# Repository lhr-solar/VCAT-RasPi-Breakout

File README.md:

# Controls-RasPi-Breakout

This is the PCB that will interface with the Raspberry Pi Compute Module 4.

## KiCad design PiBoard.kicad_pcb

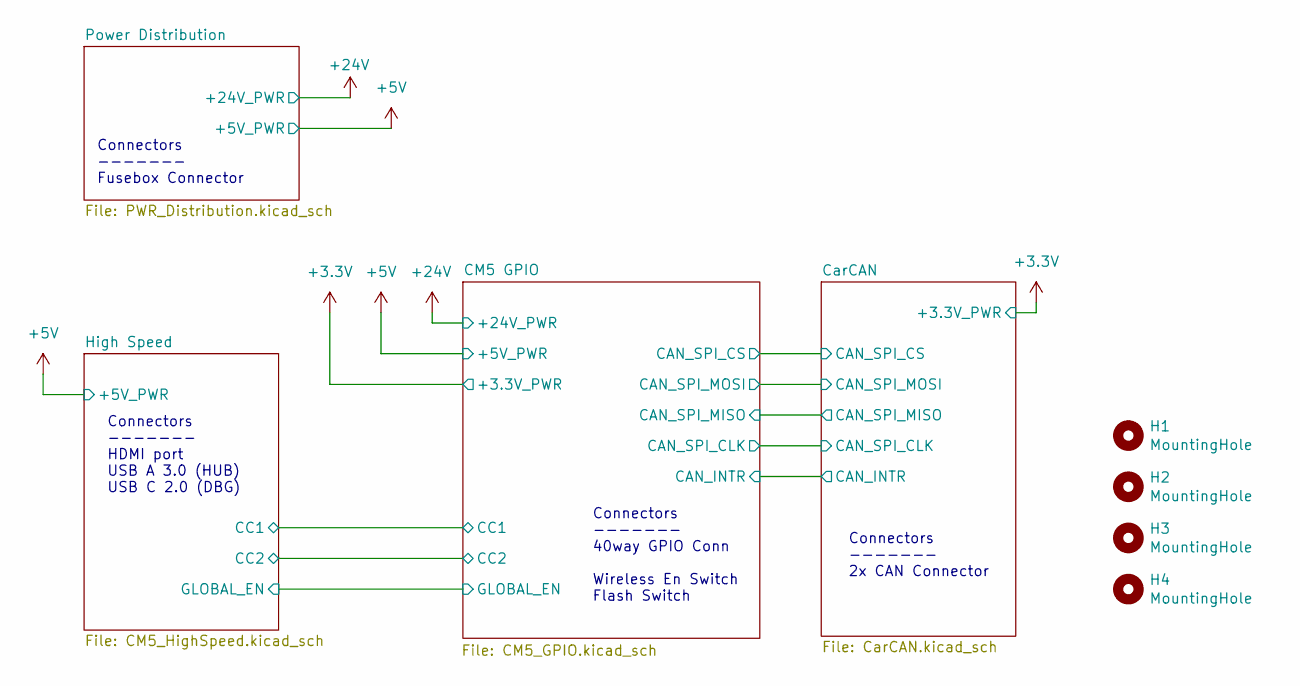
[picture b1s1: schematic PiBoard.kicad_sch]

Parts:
H1, H2, H3, H4: MountingHole; MountingHole_3.2mm_M3; JLC N/A

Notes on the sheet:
Connectors ------- HDMI port USB A 3.0 (HUB) USB C 2.0 (DBG)
Connectors ------- Fusebox Connector
Connectors ------- 2x CAN Connector
Connectors ------- 40way GPIO Conn Wireless En Switch Flash Switch

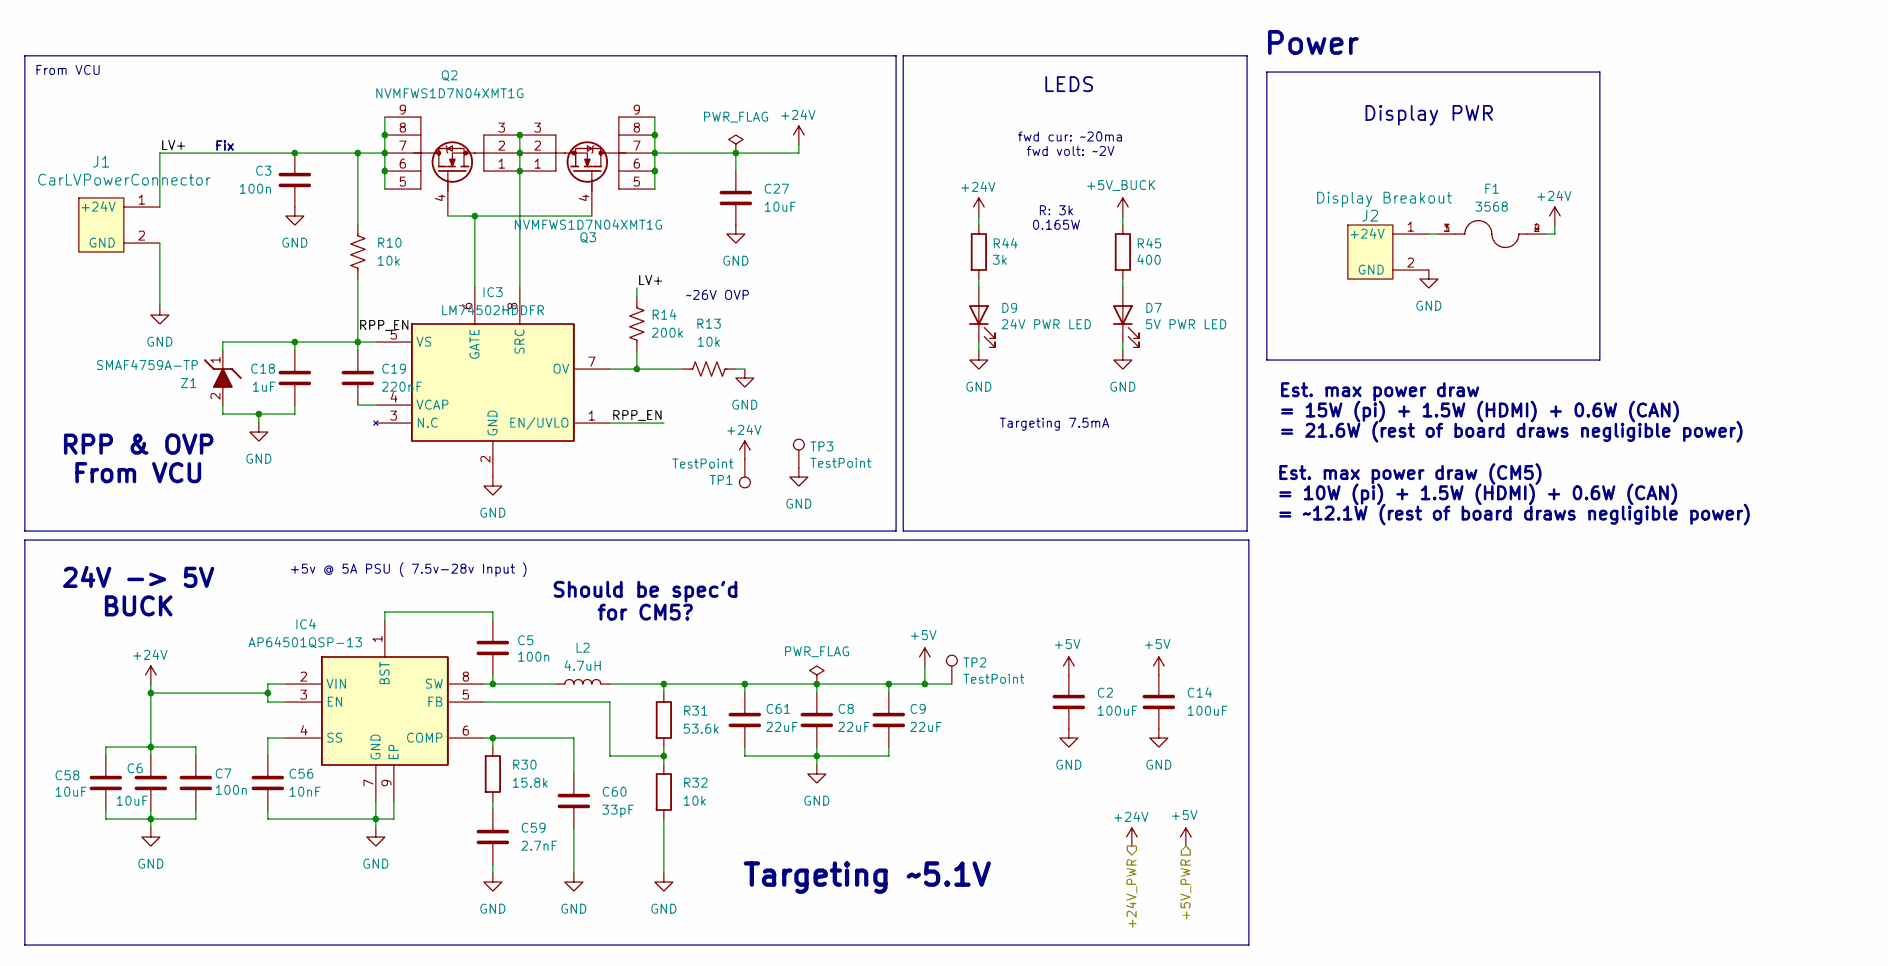
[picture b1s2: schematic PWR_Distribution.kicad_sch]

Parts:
C2, C14: 100uF; C_1206_3216Metric_Pad1.33x1.80mm_HandSolder; JLC C7432784
C3, C5, C7: 100n; C_0603_1608Metric_Pad1.08x0.95mm_HandSolder; JLC C14663
C6, C27, C58: 10uF; C_0805_2012Metric_Pad1.18x1.45mm_HandSolder; JLC C440198
C8, C9, C61: 22uF; C_0805_2012Metric_Pad1.18x1.45mm_HandSolder; JLC C338078
C18: 1uF; C_0805_2012Metric_Pad1.18x1.45mm_HandSolder; JLC C28323
C19: 220nF; C_0805_2012Metric_Pad1.18x1.45mm_HandSolder; JLC C21120
C56: 10nF; C_0603_1608Metric_Pad1.08x0.95mm_HandSolder; JLC C1589
C59: 2.7nF; C_0603_1608Metric_Pad1.08x0.95mm_HandSolder; JLC C107085
C60: 33pF; C_0603_1608Metric_Pad1.08x0.95mm_HandSolder; JLC C1663
D7: 5V PWR LED; LED_0603_1608Metric_Pad1.05x0.95mm_HandSolder; JLC C2289
D9: 24V PWR LED; LED_0603_1608Metric_Pad1.05x0.95mm_HandSolder; JLC C2289
F1: 3568; FUSE_3568; PARTREV C
IC3: LM74502HDDFR; SOT65P280X110-8N; Mouser Part Number 595-LM74502HDDFR
IC4: AP64501QSP-13; SOIC127P600X163-9N; JLC C2071517
J1: CarLVPowerConnector; Molex_Nano-Fit_105309-xx02_1x02_P2.50mm_Vertical; JLC N/A
J2: Display Breakout; Molex_Nano-Fit_105309-xx02_1x02_P2.50mm_Vertical; JLC N/A
L2: 4.7uH; INDPM110100X540N; JLC C5189748
Q2, Q3: NVMFWS1D7N04XMT1G; NVMFWS3D0P04M8LT1G; Manufacturer_Part_Number NVMFWS1D7N04XMT1G; JLC C52190853
R10, R13: 10k; R_0603_1608Metric_Pad0.98x0.95mm_HandSolder; JLC C25804
R14: 200k; R_0603_1608Metric_Pad0.98x0.95mm_HandSolder; JLC C25811
R30: 15.8k; R_0805_2012Metric_Pad1.20x1.40mm_HandSolder; JLC C17468
R31: 53.6k; R_0805_2012Metric_Pad1.20x1.40mm_HandSolder; JLC C2930115
R32: 10k; R_0805_2012Metric; JLC C17414
R44: 3k; R_0603_1608Metric_Pad0.98x0.95mm_HandSolder; JLC C445829
R45: 400; R_0603_1608Metric_Pad0.98x0.95mm_HandSolder; JLC C5841024
TP1, TP2, TP3: TestPoint; TestPoint_Pad_2.0x2.0mm; JLC N/A
Z1: SMAF4759A-TP; D_SMA; Mouser Part Number 833-SMAF4749A-TP

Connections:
+5V: C2.1, C8.1, C9.1, C14.1, C61.1, L2.2, R31.1, TP2.1; also elsewhere on the board
+5V_BUCK: R45.1
+24V: C6.1, C7.1, C27.1, C58.1, F1.2, F1.4, IC4.2 (VIN), IC4.3 (EN), Q3.5, Q3.6, Q3.7, Q3.8, Q3.9, R44.1, TP1.1
/Power Distribution/LV+: C3.2, J1.1 (+24V), Q2.5, Q2.6, Q2.7, Q2.8, Q2.9, R10.1, R14.1
/Power Distribution/RPP_EN: C18.2, C19.1, IC3.1 (EN/UVLO), IC3.5 (VS), R10.2, Z1.1 (K)
GND: C2.2, C3.1, C6.2, C7.2, C8.2, C9.2, C14.2, C18.1, C27.2, C56.2, C58.2, C59.2, C60.2, C61.2, D7.1 (K), D9.1 (K), IC3.2 (GND), IC4.7 (GND), IC4.9 (EP), J1.2 (GND), J2.2 (GND), R13.2, R32.2, TP3.1, Z1.2 (A); also elsewhere on the board
unnamed: C59.1, R30.2
unnamed: D7.2 (A), R45.2
unnamed: D9.2 (A), R44.2
unnamed: IC3.6 (GATE), Q2.4, Q3.4
unnamed: IC3.7 (OV), R13.1, R14.2
unnamed: IC3.8 (SRC), Q2.1, Q2.2, Q2.3, Q3.1, Q3.2, Q3.3
unnamed: C19.2, IC3.4 (VCAP)
unnamed: C5.1, IC4.1 (BST)
unnamed: C60.1, IC4.6 (COMP), R30.1
unnamed: IC4.5 (FB), R31.2, R32.1
unnamed: C56.1, IC4.4 (SS)
unnamed: C5.2, IC4.8 (SW), L2.1
unnamed: F1.1, F1.3, J2.1 (+24V)

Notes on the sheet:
Est. max power draw (CM5) = 10W (pi) + 1.5W (HDMI) + 0.6W (CAN) = ~12.1W (rest of board draws negligible power)
RPP & OVP From VCU
Fix
From VCU
Display PWR
Est. max power draw = 15W (pi) + 1.5W (HDMI) + 0.6W (CAN) = 21.6W (rest of board draws negligible power)
Targeting ~5.1V
Should be spec'd for CM5?
+5v @ 5A PSU ( 7.5v-28v Input )
~26V OVP
R: 3k 0.165W
LEDS
fwd cur: ~20ma fwd volt: ~2V
Targeting 7.5mA
Power
24V -> 5V BUCK

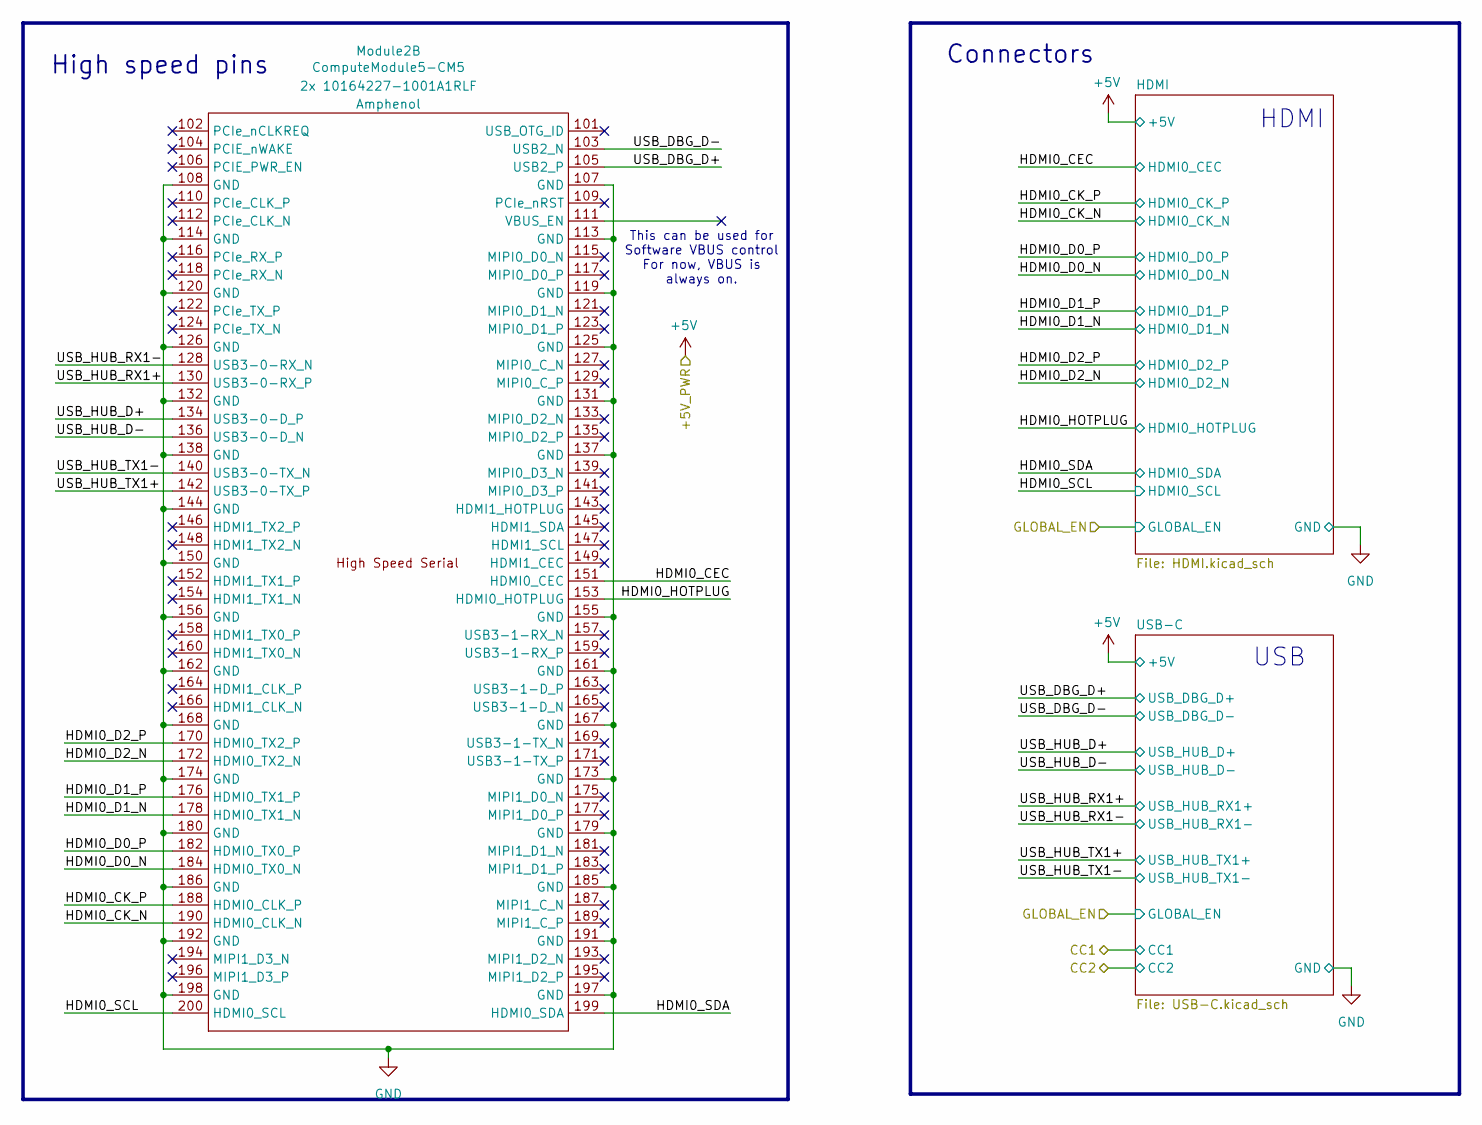
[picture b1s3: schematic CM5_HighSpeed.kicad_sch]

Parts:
Module2: ComputeModule5-CM5; Raspberry-Pi-5-Compute-Module; Part Description 100 Position Connector Receptacle, Cent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; JLC C6782225

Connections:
/High Speed/HDMI0_CEC: Module2.151 (HDMI0_CEC); also elsewhere on the board
/High Speed/HDMI0_CK_N: Module2.190 (HDMI0_CLK_N); also elsewhere on the board
/High Speed/HDMI0_CK_P: Module2.188 (HDMI0_CLK_P); also elsewhere on the board
/High Speed/HDMI0_D0_N: Module2.184 (HDMI0_TX0_N); also elsewhere on the board
/High Speed/HDMI0_D0_P: Module2.182 (HDMI0_TX0_P); also elsewhere on the board
/High Speed/HDMI0_D1_N: Module2.178 (HDMI0_TX1_N); also elsewhere on the board
/High Speed/HDMI0_D1_P: Module2.176 (HDMI0_TX1_P); also elsewhere on the board
/High Speed/HDMI0_D2_N: Module2.172 (HDMI0_TX2_N); also elsewhere on the board
/High Speed/HDMI0_D2_P: Module2.170 (HDMI0_TX2_P); also elsewhere on the board
/High Speed/HDMI0_HOTPLUG: Module2.153 (HDMI0_HOTPLUG); also elsewhere on the board
/High Speed/HDMI0_SCL: Module2.200 (HDMI0_SCL); also elsewhere on the board
/High Speed/HDMI0_SDA: Module2.199 (HDMI0_SDA); also elsewhere on the board
/High Speed/USB_DBG_D+: Module2.105 (USB2_P); also elsewhere on the board
/High Speed/USB_DBG_D-: Module2.103 (USB2_N); also elsewhere on the board
/High Speed/USB_HUB_D+: Module2.134 (USB3-0-D_P); also elsewhere on the board
/High Speed/USB_HUB_D-: Module2.136 (USB3-0-D_N); also elsewhere on the board
/High Speed/USB_HUB_RX1+: Module2.130 (USB3-0-RX_P); also elsewhere on the board
/High Speed/USB_HUB_RX1-: Module2.128 (USB3-0-RX_N); also elsewhere on the board
/High Speed/USB_HUB_TX1+: Module2.142 (USB3-0-TX_P); also elsewhere on the board
/High Speed/USB_HUB_TX1-: Module2.140 (USB3-0-TX_N); also elsewhere on the board
GND: Module2.107 (GND), Module2.108 (GND), Module2.113 (GND), Module2.114 (GND), Module2.119 (GND), Module2.120 (GND), Module2.125 (GND), Module2.126 (GND), Module2.131 (GND), Module2.132 (GND), Module2.137 (GND), Module2.138 (GND), Module2.144 (GND), Module2.150 (GND), Module2.155 (GND), Module2.156 (GND), Module2.161 (GND), Module2.162 (GND), Module2.167 (GND), Module2.168 (GND), Module2.173 (GND), Module2.174 (GND), Module2.179 (GND), Module2.180 (GND), Module2.185 (GND), Module2.186 (GND), Module2.191 (GND), Module2.192 (GND), Module2.197 (GND), Module2.198 (GND); also elsewhere on the board

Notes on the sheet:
This can be used for Software VBUS control For now, VBUS is always on.
USB
Connectors
High speed pins
HDMI

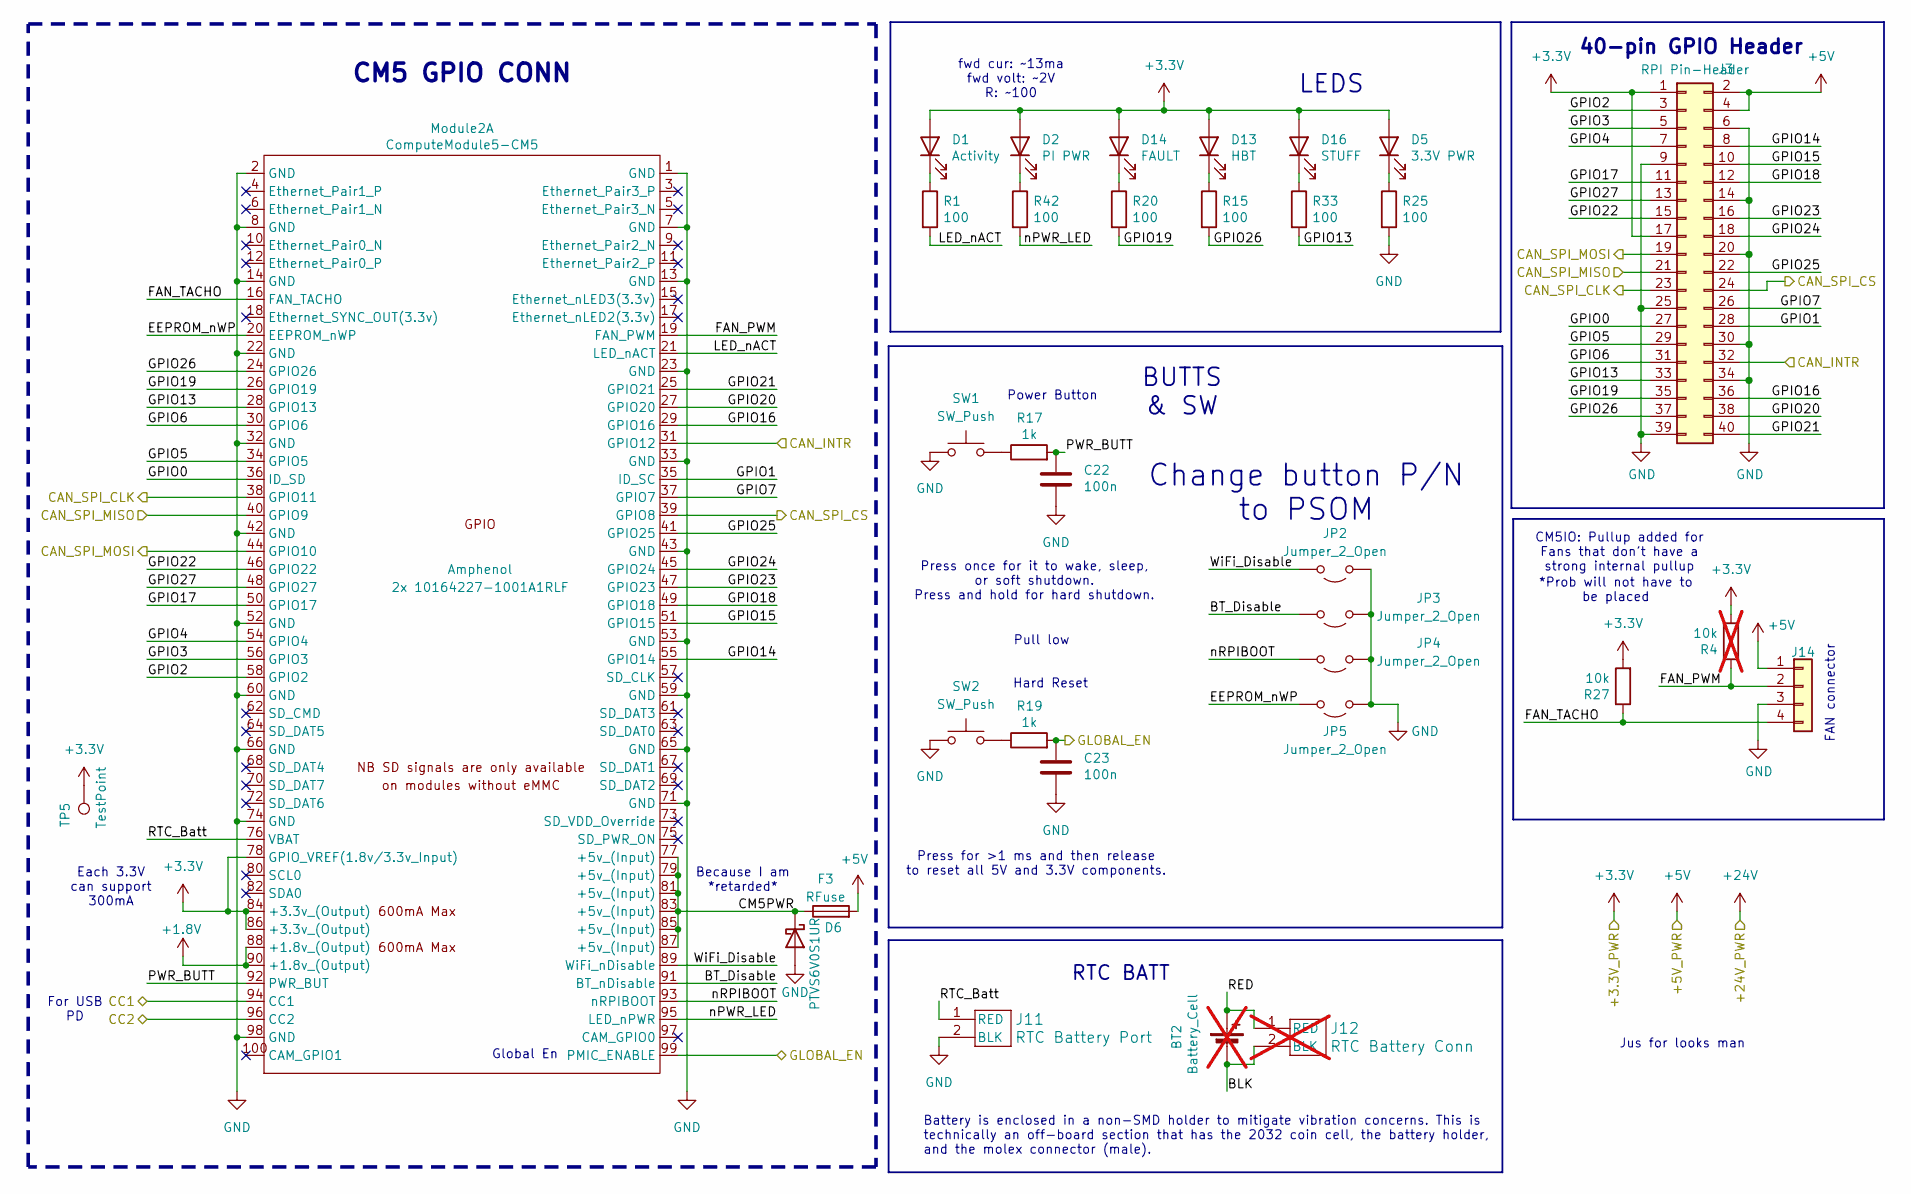
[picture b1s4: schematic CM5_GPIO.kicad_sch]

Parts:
BT2: Battery_Cell; JLC N/A; not fitted
C22, C23: 100n; C_0603_1608Metric_Pad1.08x0.95mm_HandSolder; JLC C14663
D1: Activity; LED_0603_1608Metric_Pad1.05x0.95mm_HandSolder; JLC C2289
D2: PI PWR; LED_0603_1608Metric_Pad1.05x0.95mm_HandSolder; JLC C2289
D5: 3.3V PWR; LED_0603_1608Metric_Pad1.05x0.95mm_HandSolder; JLC C2289
D6: PTVS6V0S1UR; D_SOD-123; JLC C18723426
D13: HBT; LED_0603_1608Metric_Pad1.05x0.95mm_HandSolder; JLC C2289
D14: FAULT; LED_0603_1608Metric_Pad1.05x0.95mm_HandSolder; JLC C2286
D16: STUFF; LED_0603_1608Metric_Pad1.05x0.95mm_HandSolder; JLC C2289
F3: RFuse; Fuse_1206_3216Metric_Pad1.42x1.75mm_HandSolder; JLC C42449089
J3: RPI Pin-Header; PinSocket_2x20_P2.54mm_Vertical; JLC N/A
J11: RTC Battery Port; CONN02_530470210_MOL; JLC N/A
J12: RTC Battery Conn; CONN02_530470210_MOL; JLC N/A; not fitted
J14: Fan Header; JST_SH_BM04B-SRSS-TB_1x04-1MP_P1.00mm_Vertical; Part Description 4 pin vertical 1mm pitch connector; JLC N/A
JP2, JP3, JP4, JP5: Jumper_2_Open; PinHeader_1x02_P2.54mm_Vertical; JLC N/A
Module2: ComputeModule5-CM5; Raspberry-Pi-5-Compute-Module; Part Description 100 Position Connector Receptacle, Cent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; JLC C6782225
R1, R15, R20, R25, R33, R42: 100; R_0603_1608Metric_Pad0.98x0.95mm_HandSolder; JLC C22775
R4: 10k; R_0603_1608Metric_Pad0.98x0.95mm_HandSolder; Part Description Resistor 10K M1005 1% 63mW; JLC C25804; not fitted
R17, R19: 1k; R_0603_1608Metric_Pad0.98x0.95mm_HandSolder; JLC C21190
R27: 10k; R_0603_1608Metric_Pad0.98x0.95mm_HandSolder; Part Description Resistor 10K M1005 1% 63mW; JLC C25804
SW1, SW2: SW_Push; TL3365AF180QG; JLC C2886926
TP5: TestPoint; TestPoint_Pad_2.0x2.0mm; JLC N/A

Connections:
+1.8V: Module2.88 (+1.8v_(Output)), Module2.90 (+1.8v_(Output))
+3.3V: D1.2 (A), D2.2 (A), D5.2 (A), D13.2 (A), D14.2 (A), D16.2 (A), J3.1, J3.17, Module2.78 (GPIO_VREF(1.8v/3.3v_Input)), Module2.84 (+3.3v_(Output)), Module2.86 (+3.3v_(Output)), R4.2, R27.2, TP5.1; also elsewhere on the board
+5V: F3.2, J3.2, J3.4, J14.1; also elsewhere on the board
/CM5 GPIO/BT_Disable: JP3.2 (B), Module2.91 (BT_nDisable)
/CM5 GPIO/CAN_INTR: J3.32, Module2.31 (GPIO12); also elsewhere on the board
/CM5 GPIO/CAN_SPI_CLK: J3.23, Module2.38 (GPIO11); also elsewhere on the board
/CM5 GPIO/CAN_SPI_CS: J3.24, Module2.39 (GPIO8); also elsewhere on the board
/CM5 GPIO/CAN_SPI_MISO: J3.21, Module2.40 (GPIO9); also elsewhere on the board
/CM5 GPIO/CAN_SPI_MOSI: J3.19, Module2.44 (GPIO10); also elsewhere on the board
/CM5 GPIO/CC1: Module2.94 (CC1); also elsewhere on the board
/CM5 GPIO/CC2: Module2.96 (CC2); also elsewhere on the board
/CM5 GPIO/CM5PWR: D6.1 (K), F3.1, Module2.77 (+5v_(Input)), Module2.79 (+5v_(Input)), Module2.81 (+5v_(Input)), Module2.83 (+5v_(Input)), Module2.85 (+5v_(Input)), Module2.87 (+5v_(Input))
/CM5 GPIO/EEPROM_nWP: JP5.2 (B), Module2.20 (EEPROM_nWP)
/CM5 GPIO/FAN_PWM: J14.2, Module2.19 (FAN_PWM), R4.1
/CM5 GPIO/FAN_TACHO: J14.4, Module2.16 (FAN_TACHO), R27.1
/CM5 GPIO/GLOBAL_EN: C23.1, Module2.99 (PMIC_ENABLE), R19.2; also elsewhere on the board
/CM5 GPIO/GPIO0: J3.27, Module2.36 (ID_SD)
/CM5 GPIO/GPIO1: J3.28, Module2.35 (ID_SC)
/CM5 GPIO/GPIO2: J3.3, Module2.58 (GPIO2)
/CM5 GPIO/GPIO3: J3.5, Module2.56 (GPIO3)
/CM5 GPIO/GPIO4: J3.7, Module2.54 (GPIO4)
/CM5 GPIO/GPIO5: J3.29, Module2.34 (GPIO5)
/CM5 GPIO/GPIO6: J3.31, Module2.30 (GPIO6)
/CM5 GPIO/GPIO7: J3.26, Module2.37 (GPIO7)
/CM5 GPIO/GPIO13: J3.33, Module2.28 (GPIO13), R33.2
/CM5 GPIO/GPIO14: J3.8, Module2.55 (GPIO14)
/CM5 GPIO/GPIO15: J3.10, Module2.51 (GPIO15)
/CM5 GPIO/GPIO16: J3.36, Module2.29 (GPIO16)
/CM5 GPIO/GPIO17: J3.11, Module2.50 (GPIO17)
/CM5 GPIO/GPIO18: J3.12, Module2.49 (GPIO18)
/CM5 GPIO/GPIO19: J3.35, Module2.26 (GPIO19), R20.2
/CM5 GPIO/GPIO20: J3.38, Module2.27 (GPIO20)
/CM5 GPIO/GPIO21: J3.40, Module2.25 (GPIO21)
/CM5 GPIO/GPIO22: J3.15, Module2.46 (GPIO22)
/CM5 GPIO/GPIO23: J3.16, Module2.47 (GPIO23)
/CM5 GPIO/GPIO24: J3.18, Module2.45 (GPIO24)
/CM5 GPIO/GPIO25: J3.22, Module2.41 (GPIO25)
/CM5 GPIO/GPIO26: J3.37, Module2.24 (GPIO26), R15.2
/CM5 GPIO/GPIO27: J3.13, Module2.48 (GPIO27)
/CM5 GPIO/LED_nACT: Module2.21 (LED_nACT), R1.2
/CM5 GPIO/PWR_BUTT: C22.1, Module2.92 (PWR_BUT), R17.2
/CM5 GPIO/RTC_Batt: J11.1 (RED), Module2.76 (VBAT)
/CM5 GPIO/WiFi_Disable: JP2.2 (B), Module2.89 (WiFi_nDisable)
/CM5 GPIO/nPWR_LED: Module2.95 (LED_nPWR), R42.2
/CM5 GPIO/nRPIBOOT: JP4.2 (B), Module2.93 (nRPIBOOT)
GND: C22.2, C23.2, D6.2 (A), J3.6, J3.9, J3.14, J3.20, J3.25, J3.30, J3.34, J3.39, J11.2 (BLK), J14.3, JP2.1 (A), JP3.1 (A), JP4.1 (A), JP5.1 (A), Module2.1 (GND), Module2.2 (GND), Module2.7 (GND), Module2.8 (GND), Module2.13 (GND), Module2.14 (GND), Module2.22 (GND), Module2.23 (GND), Module2.32 (GND), Module2.33 (GND), Module2.42 (GND), Module2.43 (GND), Module2.52 (GND), Module2.53 (GND), Module2.59 (GND), Module2.60 (GND), Module2.65 (GND), Module2.66 (GND), Module2.71 (GND), Module2.74 (GND), Module2.98 (GND), R25.2, SW1.1, SW2.1; also elsewhere on the board
unnamed: BT2.1 (+), J12.1 (RED)
unnamed: BT2.2 (-), J12.2 (BLK)
unnamed: D1.1 (K), R1.1
unnamed: D2.1 (K), R42.1
unnamed: D5.1 (K), R25.1
unnamed: D13.1 (K), R15.1
unnamed: D14.1 (K), R20.1
unnamed: D16.1 (K), R33.1
unnamed: R17.1, SW1.2
unnamed: R19.1, SW2.2

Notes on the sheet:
Press once for it to wake, sleep, or soft shutdown. Press and hold for hard shutdown.
Power Button
FAN connector
fwd cur: ~13ma fwd volt: ~2V R: ~100
*Prob will not have to be placed
LEDS
Battery is enclosed in a non-SMD holder to mitigate vibration concerns. This is technically an off-board section that has the 2032 coin cell, the battery holder, and the molex connector (male).
Change button P/N to PSOM
Global En
For USB PD
40-pin GPIO Header
Each 3.3V can support 300mA
Because I am *retarded*
Jus for looks man
CM5 GPIO CONN
Hard Reset
BUTTS & SW
Press for >1 ms and then release to reset all 5V and 3.3V components.
CM5IO: Pullup added for Fans that don't have a strong internal pullup
Pull low
RTC BATT

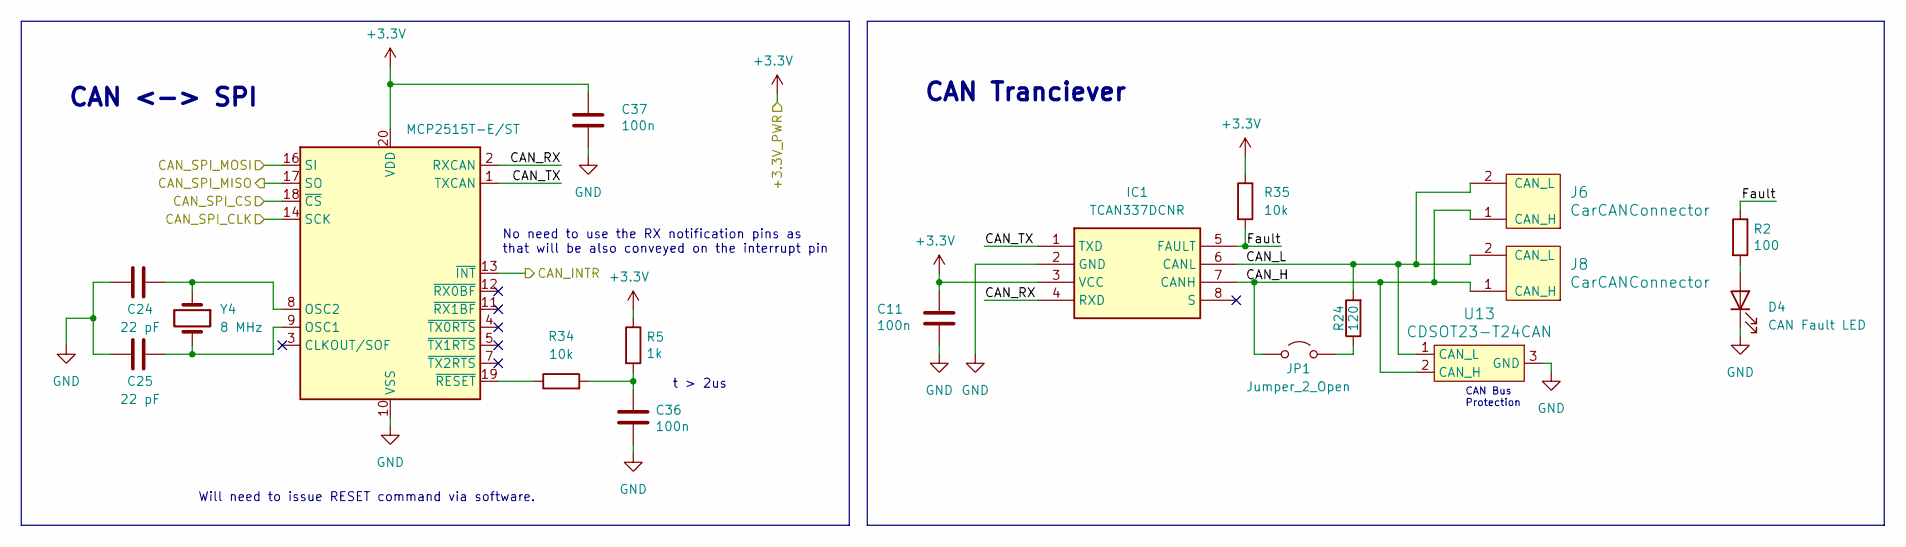
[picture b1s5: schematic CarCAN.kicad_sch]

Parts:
C11, C36, C37: 100n; C_0603_1608Metric_Pad1.08x0.95mm_HandSolder; JLC C14663
C24, C25: 22 pF; C_0603_1608Metric_Pad1.08x0.95mm_HandSolder; JLC C1653
D4: CAN Fault LED; LED_0603_1608Metric_Pad1.05x0.95mm_HandSolder; JLC C2286
IC1: TCAN337DCNR; SOT65P280X145-8N; JLC C130129
J6, J8: CarCANConnector; Molex_Nano-Fit_105309-xx02_1x02_P2.50mm_Vertical; JLC N/A
JP1: Jumper_2_Open; PinHeader_1x02_P2.54mm_Vertical; JLC N/A
R2: 100; R_0603_1608Metric_Pad0.98x0.95mm_HandSolder; JLC C22775
R5: 1k; R_0603_1608Metric_Pad0.98x0.95mm_HandSolder; JLC C21190
R24: 120; R_0603_1608Metric_Pad0.98x0.95mm_HandSolder; JLC C22787
R34, R35: 10k; R_0603_1608Metric_Pad0.98x0.95mm_HandSolder; JLC C25804
U13: CDSOT23-T24CAN; SOT-23W; JLC C2959841
U14: MCP2515T-E/ST; TSSOP-20_4.4x6.5mm_P0.65mm; JLC C627064
Y4: 8 MHz; ABM3; JLC C144380

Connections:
+3.3V: C11.1, C37.1, IC1.3 (VCC), R5.1, R35.1, U14.20 (VDD); also elsewhere on the board
/CM5 GPIO/CAN_INTR: U14.13 (~INT); also elsewhere on the board
/CM5 GPIO/CAN_SPI_CLK: U14.14 (SCK); also elsewhere on the board
/CM5 GPIO/CAN_SPI_CS: U14.18 (~CS); also elsewhere on the board
/CM5 GPIO/CAN_SPI_MISO: U14.17 (SO); also elsewhere on the board
/CM5 GPIO/CAN_SPI_MOSI: U14.16 (SI); also elsewhere on the board
/CarCAN/CAN_H: IC1.7 (CANH), J6.1 (CAN_H), J8.1 (CAN_H), JP1.1 (A), U13.2 (CAN_H)
/CarCAN/CAN_L: IC1.6 (CANL), J6.2 (CAN_L), J8.2 (CAN_L), R24.2, U13.1 (CAN_L)
/CarCAN/CAN_RX: IC1.4 (RXD), U14.2 (RXCAN)
/CarCAN/CAN_TX: IC1.1 (TXD), U14.1 (TXCAN)
/CarCAN/Fault: IC1.5 (FAULT), R2.1, R35.2
GND: C11.2, C24.1, C25.1, C36.2, C37.2, D4.1 (K), IC1.2 (GND), U13.3 (GND), U14.10 (VSS); also elsewhere on the board
unnamed: C36.1, R5.2, R34.2
unnamed: D4.2 (A), R2.2
unnamed: JP1.2 (B), R24.1
unnamed: C25.2, U14.9 (OSC1), Y4.2
unnamed: C24.2, U14.8 (OSC2), Y4.1
unnamed: R34.1, U14.19 (~RESET)

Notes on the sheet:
CAN Tranciever
t > 2us
No need to use the RX notification pins as that will be also conveyed on the interrupt pin
CAN <-> SPI
CAN Bus Protection
Will need to issue RESET command via software.

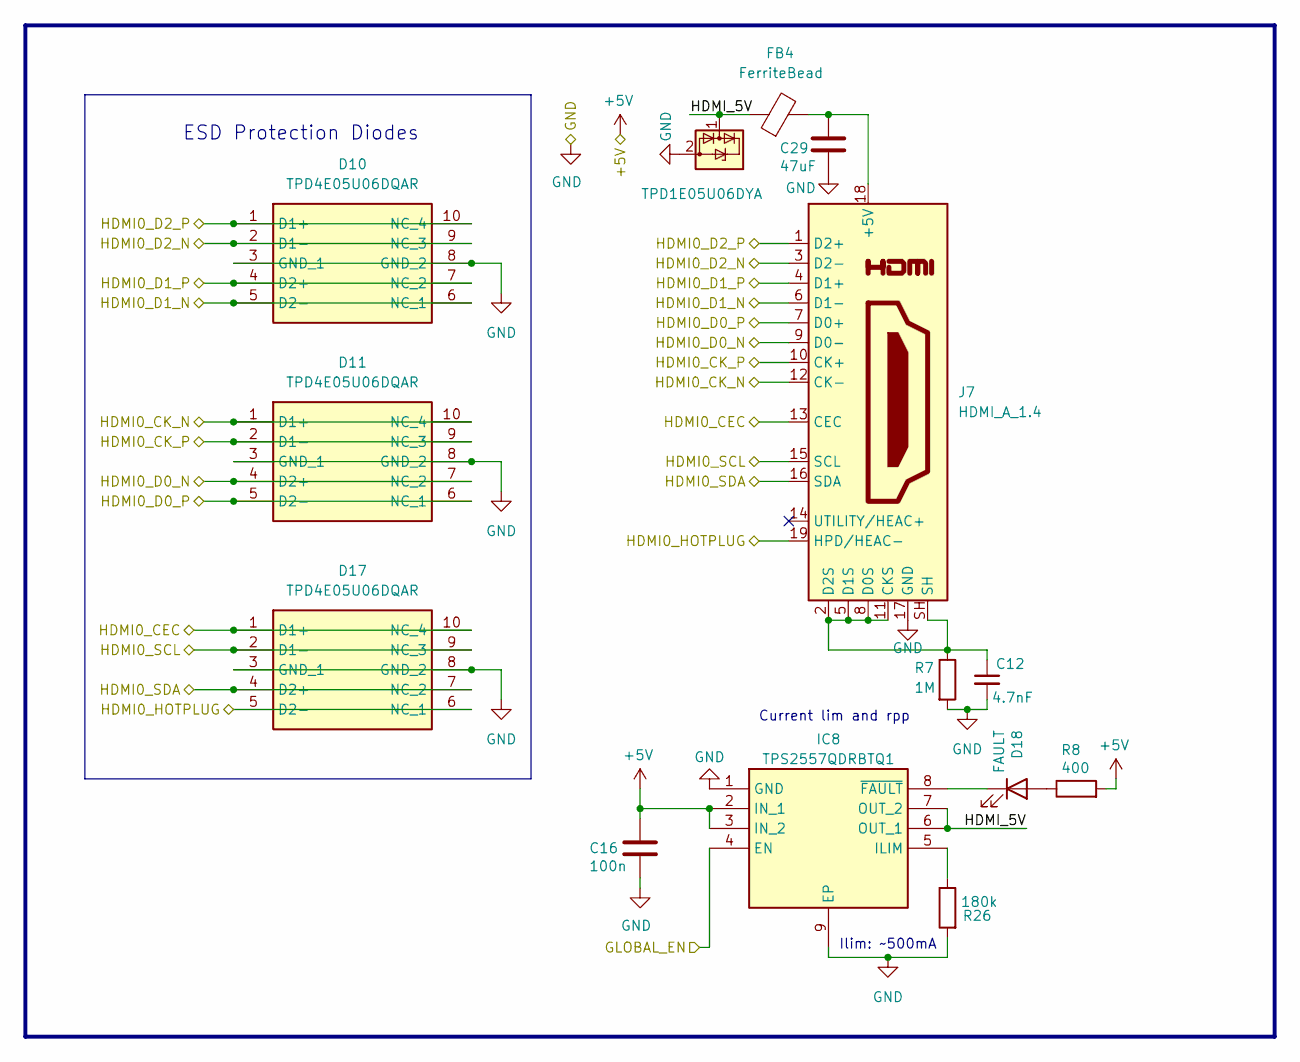
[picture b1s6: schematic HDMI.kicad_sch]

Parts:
C12: 4.7nF; C_0603_1608Metric_Pad1.08x0.95mm_HandSolder; JLC C696859
C16: 100n; C_0603_1608Metric_Pad1.08x0.95mm_HandSolder; JLC C14663
C29: 47uF; C_0805_2012Metric_Pad1.18x1.45mm_HandSolder; JLC C16780
D10, D11, D17: TPD4E05U06DQAR; IC_TPD4E05U06QDQARQ1; JLC C138714
D18: FAULT; LED_0603_1608Metric_Pad1.05x0.95mm_HandSolder; JLC C2286
FB4: FerriteBead; L_0805_2012Metric_Pad1.05x1.20mm_HandSolder; JLC C1015
IC8: TPS2557QDRBTQ1; SON65P300X300X100-9N-D; Mouser Part Number 595-TPS2557QDRBTQ1
J7: HDMI_A_1.4; HDMI_A_Molex_208658-1001_Horizontal; JLC C916313
R7: 1M; R_0603_1608Metric_Pad0.98x0.95mm_HandSolder; JLC C22935
R8: 400; R_0603_1608Metric_Pad0.98x0.95mm_HandSolder; JLC C5841024
R26: 180k; R_0603_1608Metric_Pad0.98x0.95mm_HandSolder; JLC C22356446
U1: TPD1E05U06DYA; D_SOD-523; JLC TPD1E05U06DYAR

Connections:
+5V: C16.1, IC8.2 (IN_1), IC8.3 (IN_2), R8.2; also elsewhere on the board
/CM5 GPIO/GLOBAL_EN: IC8.4 (EN); also elsewhere on the board
/High Speed/HDMI0_CEC: D17.1 (D1+), D17.10 (NC_4), J7.13 (CEC); also elsewhere on the board
/High Speed/HDMI0_CK_N: D11.1 (D1+), D11.10 (NC_4), J7.12 (CK-); also elsewhere on the board
/High Speed/HDMI0_CK_P: D11.2 (D1-), D11.9 (NC_3), J7.10 (CK+); also elsewhere on the board
/High Speed/HDMI0_D0_N: D11.4 (D2+), D11.7 (NC_2), J7.9 (D0-); also elsewhere on the board
/High Speed/HDMI0_D0_P: D11.5 (D2-), D11.6 (NC_1), J7.7 (D0+); also elsewhere on the board
/High Speed/HDMI0_D1_N: D10.5 (D2-), D10.6 (NC_1), J7.6 (D1-); also elsewhere on the board
/High Speed/HDMI0_D1_P: D10.4 (D2+), D10.7 (NC_2), J7.4 (D1+); also elsewhere on the board
/High Speed/HDMI0_D2_N: D10.2 (D1-), D10.9 (NC_3), J7.3 (D2-); also elsewhere on the board
/High Speed/HDMI0_D2_P: D10.1 (D1+), D10.10 (NC_4), J7.1 (D2+); also elsewhere on the board
/High Speed/HDMI0_HOTPLUG: D17.5 (D2-), D17.6 (NC_1), J7.19 (HPD/HEAC-); also elsewhere on the board
/High Speed/HDMI0_SCL: D17.2 (D1-), D17.9 (NC_3), J7.15 (SCL); also elsewhere on the board
/High Speed/HDMI0_SDA: D17.4 (D2+), D17.7 (NC_2), J7.16 (SDA); also elsewhere on the board
/High Speed/HDMI/HDMI_5V: FB4.1, IC8.6 (OUT_1), IC8.7 (OUT_2), U1.1 (I/O)
GND: C12.2, C16.2, C29.2, D10.3 (GND_1), D10.8 (GND_2), D11.3 (GND_1), D11.8 (GND_2), D17.3 (GND_1), D17.8 (GND_2), IC8.1 (GND), IC8.9 (EP), J7.17 (GND), R7.2, R26.2, U1.2 (GND); also elsewhere on the board
unnamed: D18.2 (A), R8.1
unnamed: D18.1 (K), IC8.8 (~FAULT)
unnamed: IC8.5 (ILIM), R26.1
unnamed: C29.1, FB4.2, J7.18 (+5V)
unnamed: C12.1, J7.2 (D2S), J7.5 (D1S), J7.8 (D0S), J7.11 (CKS), J7.SH, R7.1

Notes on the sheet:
Current lim and rpp
ESD Protection Diodes
Ilim: ~500mA
